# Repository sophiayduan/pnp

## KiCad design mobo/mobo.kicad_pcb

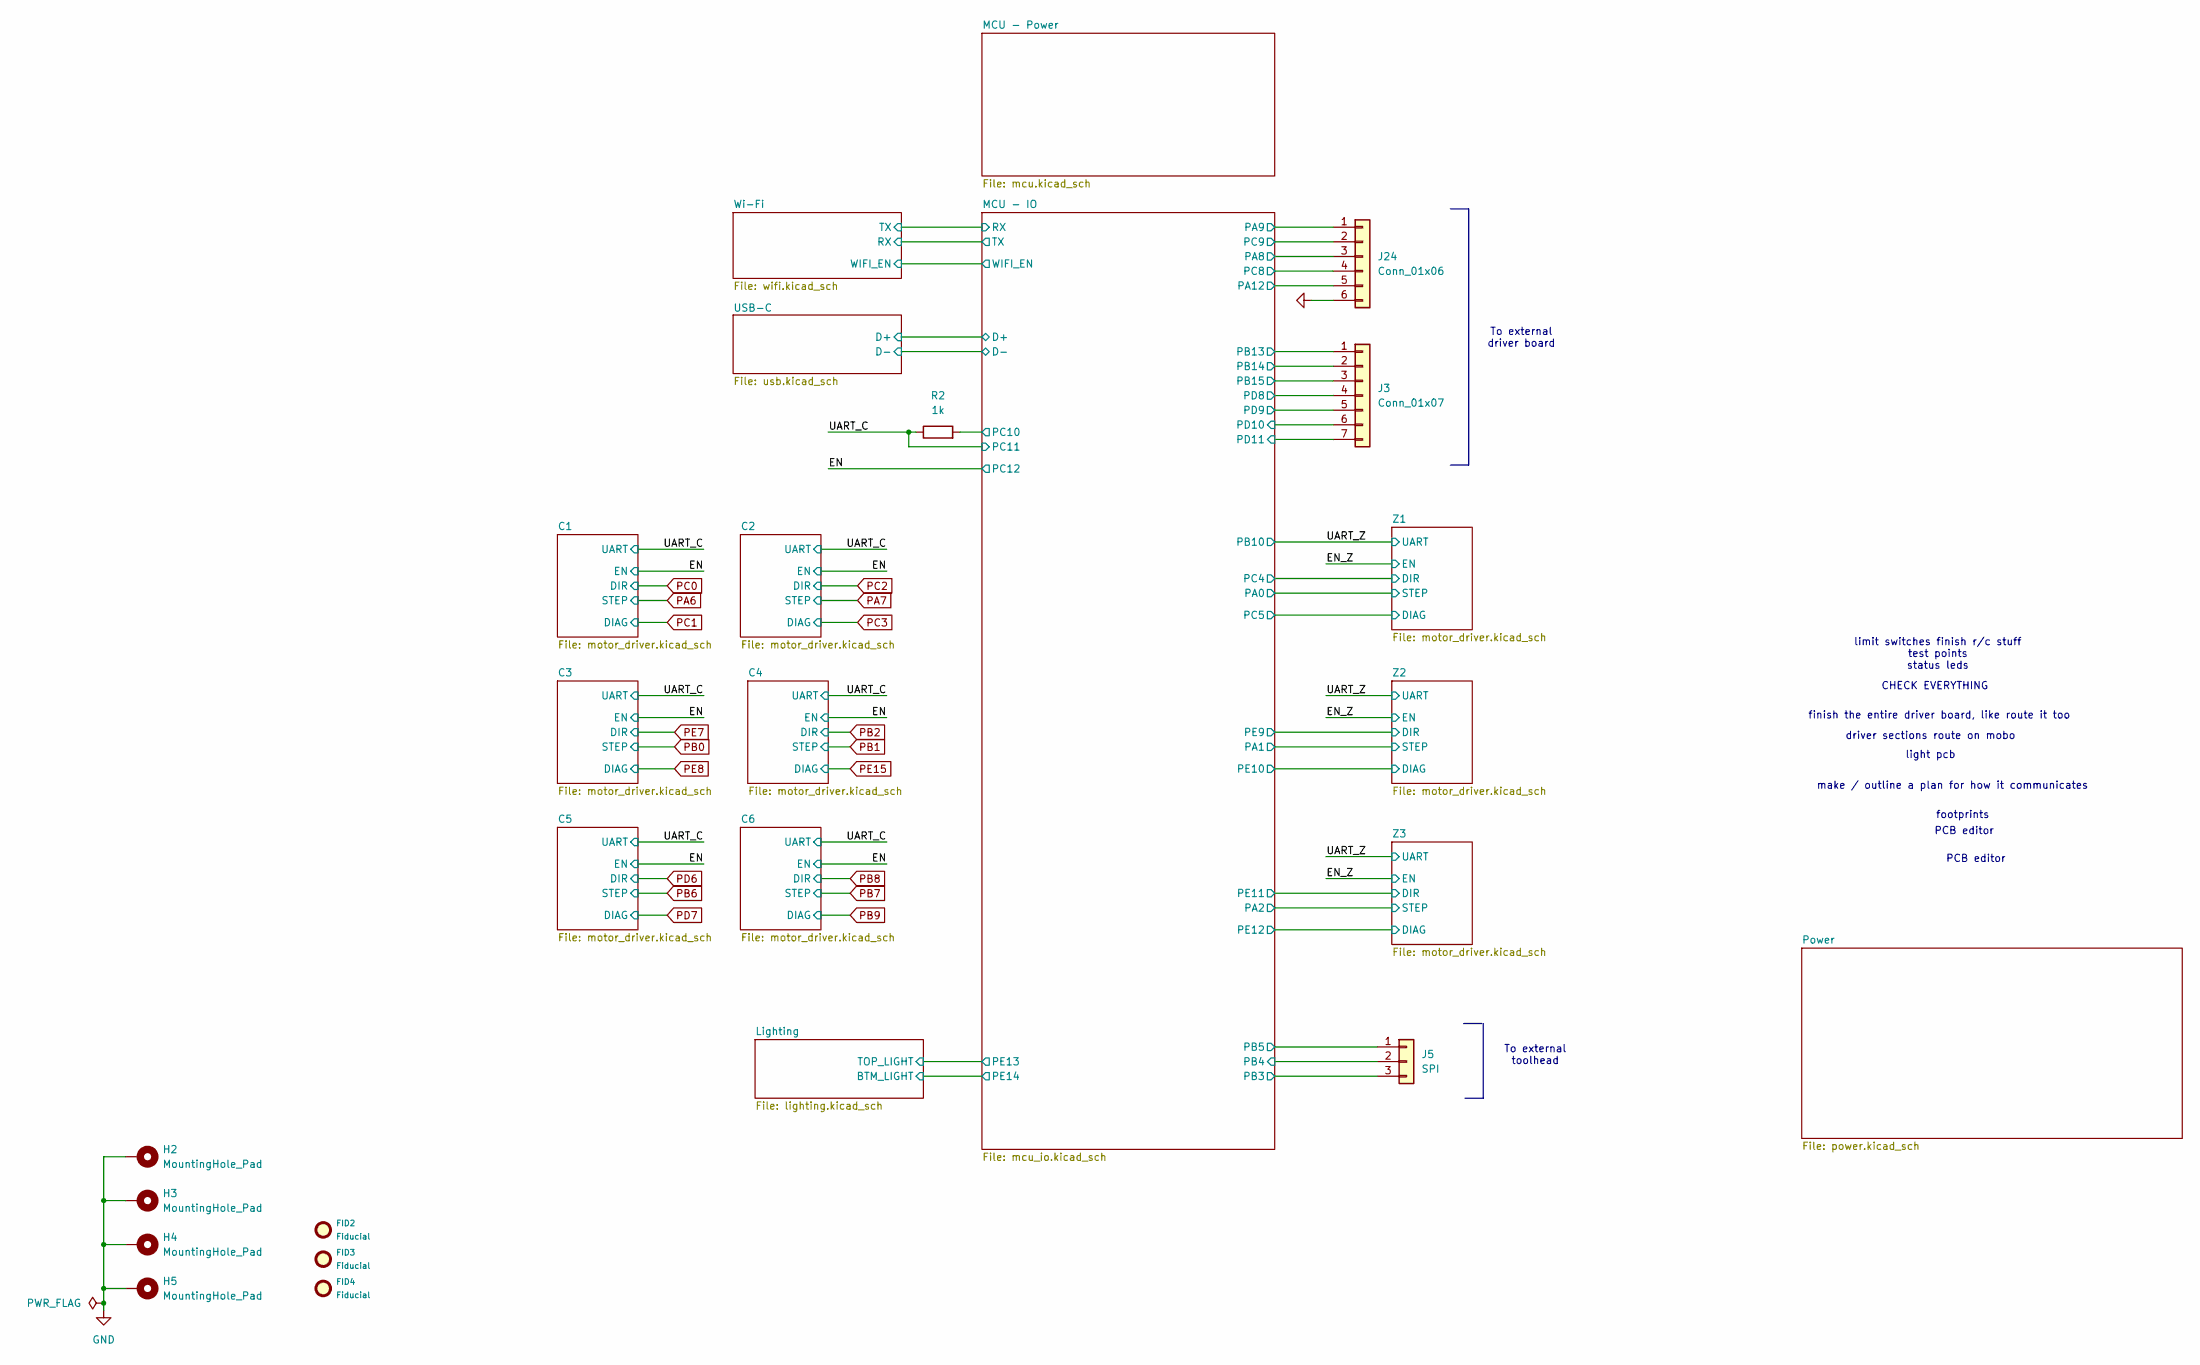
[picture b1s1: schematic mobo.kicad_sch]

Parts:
FID2, FID3, FID4: Fiducial; Fiducial_1mm_Mask2mm
H2, H3, H4, H5: MountingHole_Pad; MountingHole_2.2mm_M2_Pad_Via
J3: Conn_01x07; JST_XH_B7B-XH-A_1x07_P2.50mm_Vertical
J5: SPI; JST_EH_S3B-EH_1x03_P2.50mm_Horizontal
J24: Conn_01x06; JST_XH_B6B-XH-A_1x06_P2.50mm_Vertical
R2: 1k; R_0402_1005Metric

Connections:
/MCU - IO/PA8: J24.3; also elsewhere on the board
/MCU - IO/PA9: J24.1; also elsewhere on the board
/MCU - IO/PA12: J24.5; also elsewhere on the board
/MCU - IO/PB3: J5.3; also elsewhere on the board
/MCU - IO/PB4: J5.2; also elsewhere on the board
/MCU - IO/PB5: J5.1; also elsewhere on the board
/MCU - IO/PB13: J3.1; also elsewhere on the board
/MCU - IO/PB14: J3.2; also elsewhere on the board
/MCU - IO/PB15: J3.3; also elsewhere on the board
/MCU - IO/PC8: J24.4; also elsewhere on the board
/MCU - IO/PC9: J24.2; also elsewhere on the board
/MCU - IO/PC10: R2.2; also elsewhere on the board
/MCU - IO/PD8: J3.4; also elsewhere on the board
/MCU - IO/PD9: J3.5; also elsewhere on the board
/MCU - IO/PD10: J3.6; also elsewhere on the board
/MCU - IO/PD11: J3.7; also elsewhere on the board
/UART_C: R2.1; also elsewhere on the board
GND: H2.1, H3.1, H4.1, H5.1, J24.6; also elsewhere on the board

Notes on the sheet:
driver sections route on mobo
PCB editor
To external toolhead
light pcb
limit switches finish r/c stuff test points status leds
CHECK EVERYTHING
To external driver board
footprints
finish the entire driver board, like route it too
make / outline a plan for how it communicates

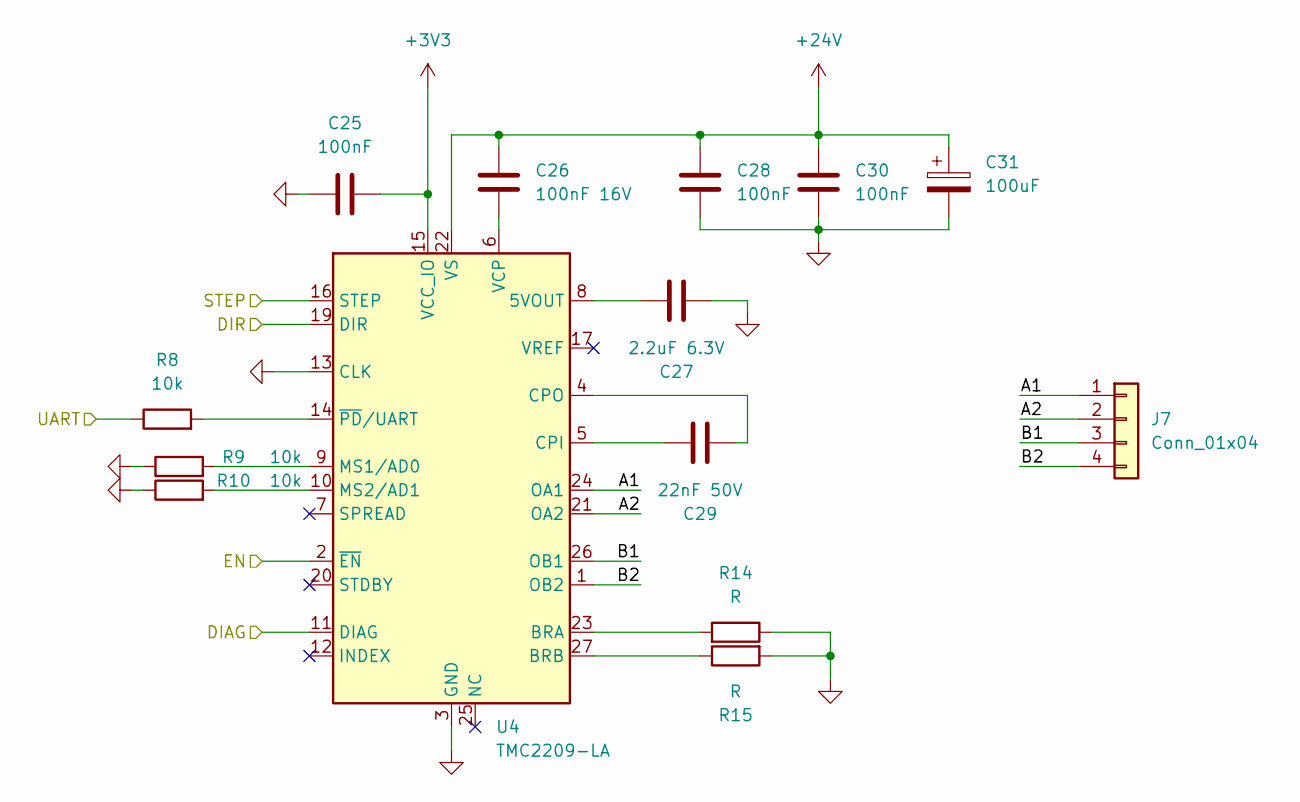
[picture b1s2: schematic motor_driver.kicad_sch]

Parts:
C25, C28: 100nF; C_0603_1608Metric
C26: 100nF 16V; C_0402_1005Metric
C27: 2.2uF 6.3V; C_0805_2012Metric
C29: 22nF 50V; C_0402_1005Metric
C30: 100nF; C_0402_1005Metric
C31: 100uF; CP_Elec_6.3x5.8
J7: Conn_01x04; JST_PH_B4B-PH-SM4-TB_1x04-1MP_P2.00mm_Vertical
R8, R9, R10: 10k; R_0402_1005Metric
R14, R15: R; R_1206_3216Metric
U4: TMC2209-LA; VQFN-28-1EP_5x5mm_P0.5mm_EP3.7x3.7mm_ThermalVias

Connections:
+3V3: C25.2, U4.15 (VCC_IO); also elsewhere on the board
+24V: C26.2, C28.2, C30.2, C31.1, U4.22 (VS), U4.28 (VS); also elsewhere on the board
/EN_Z: U4.2 (~EN); also elsewhere on the board
/MCU - IO/PA1: U4.16 (STEP); also elsewhere on the board
/MCU - IO/PE9: U4.19 (DIR); also elsewhere on the board
/MCU - IO/PE10: U4.11 (DIAG); also elsewhere on the board
/UART_Z: R8.1; also elsewhere on the board
/Z2/A1: J7.1, U4.24 (OA1)
/Z2/A2: J7.2, U4.21 (OA2)
/Z2/B1: J7.3, U4.26 (OB1)
/Z2/B2: J7.4, U4.1 (OB2)
GND: C25.1, C27.2, C28.1, C30.1, C31.2, R9.1, R10.1, R14.1, R15.2, U4.3 (GND), U4.13 (CLK), U4.18 (GND), U4.29 (GND); also elsewhere on the board
unnamed: C27.1, U4.8 (5VOUT)
unnamed: R14.2, U4.23 (BRA)
unnamed: R15.1, U4.27 (BRB)
unnamed: C29.2, U4.5 (CPI)
unnamed: C29.1, U4.4 (CPO)
unnamed: R9.2, U4.9 (MS1/AD0)
unnamed: R10.2, U4.10 (MS2/AD1)
unnamed: C26.1, U4.6 (VCP)
unnamed: R8.2, U4.14 (~PD/UART)

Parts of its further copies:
C32, C35, C46, C50, C53, C56, C60, C63, C69, C72, C76, C79, C83, C86, C121, C124: 100nF; C_0603_1608Metric
C33, C47, C54, C61, C70, C77, C84, C122: 100nF 16V; C_0402_1005Metric
C34, C48, C55, C62, C71, C78, C85, C123: 2.2uF 6.3V; C_0805_2012Metric
C36, C49, C57, C64, C73, C80, C87, C125: 22nF 50V; C_0402_1005Metric
C37, C51, C58, C65, C74, C81, C88, C126: 100nF; C_0402_1005Metric
C38, C52, C59, C66, C75, C82, C89, C127: 100uF; CP_Elec_6.3x5.8
J8, J10, J11, J12, J14, J15, J16, J22: Conn_01x04; JST_PH_B4B-PH-SM4-TB_1x04-1MP_P2.00mm_Vertical
R11, R12, R13, R17, R18, R19, R22, R23, R24, R25, R26, R29, R32, R33, R34, R37, R38, R39, R40, R41, R44, R72, R73, R74: 10k; R_0402_1005Metric
R16, R20, R21, R27, R28, R30, R31, R35, R36, R42, R43, R45, R46, R66, R75, R76: R; R_1206_3216Metric
U5, U7, U8, U9, U10, U11, U12, U19: TMC2209-LA; VQFN-28-1EP_5x5mm_P0.5mm_EP3.7x3.7mm_ThermalVias

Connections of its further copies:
+3V3: C32.2, C46.2, C53.2, C60.2, C69.2, C76.2, C83.2, C121.2, U5.15 (VCC_IO), U7.15 (VCC_IO), U8.15 (VCC_IO), U9.15 (VCC_IO), U10.15 (VCC_IO), U11.15 (VCC_IO), U12.15 (VCC_IO), U19.15 (VCC_IO); also elsewhere on the board
+24V: C33.2, C35.2, C37.2, C38.1, C47.2, C50.2, C51.2, C52.1, C54.2, C56.2, C58.2, C59.1, C61.2, C63.2, C65.2, C66.1, C70.2, C72.2, C74.2, C75.1, C77.2, C79.2, C81.2, C82.1, C84.2, C86.2, C88.2, C89.1, C122.2, C124.2, C126.2, C127.1, U5.22 (VS), U5.28 (VS), U7.22 (VS), U7.28 (VS), U8.22 (VS), U8.28 (VS), U9.22 (VS), U9.28 (VS), U10.22 (VS), U10.28 (VS), U11.22 (VS), U11.28 (VS), U12.22 (VS), U12.28 (VS), U19.22 (VS), U19.28 (VS); also elsewhere on the board
/C1/A1: J11.1, U8.24 (OA1)
/C1/A2: J11.2, U8.21 (OA2)
/C1/B1: J11.3, U8.26 (OB1)
/C1/B2: J11.4, U8.1 (OB2)
/C2/A1: J10.1, U7.24 (OA1)
/C2/A2: J10.2, U7.21 (OA2)
/C2/B1: J10.3, U7.26 (OB1)
/C2/B2: J10.4, U7.1 (OB2)
/C3/A1: J12.1, U9.24 (OA1)
/C3/A2: J12.2, U9.21 (OA2)
/C3/B1: J12.3, U9.26 (OB1)
/C3/B2: J12.4, U9.1 (OB2)
/C4/A1: J14.1, U10.24 (OA1)
/C4/A2: J14.2, U10.21 (OA2)
/C4/B1: J14.3, U10.26 (OB1)
/C4/B2: J14.4, U10.1 (OB2)
/C5/A1: J16.1, U12.24 (OA1)
/C5/A2: J16.2, U12.21 (OA2)
/C5/B1: J16.3, U12.26 (OB1)
/C5/B2: J16.4, U12.1 (OB2)
/C6/A1: J15.1, U11.24 (OA1)
/C6/A2: J15.2, U11.21 (OA2)
/C6/B1: J15.3, U11.26 (OB1)
/C6/B2: J15.4, U11.1 (OB2)
/EN: U7.2 (~EN), U8.2 (~EN), U9.2 (~EN), U10.2 (~EN), U11.2 (~EN), U12.2 (~EN); also elsewhere on the board
/EN_Z: U5.2 (~EN), U19.2 (~EN); also elsewhere on the board
/MCU - IO/PA0: U19.16 (STEP); also elsewhere on the board
/MCU - IO/PA2: U5.16 (STEP); also elsewhere on the board
/MCU - IO/PC4: U19.19 (DIR); also elsewhere on the board
/MCU - IO/PC5: U19.11 (DIAG); also elsewhere on the board
/MCU - IO/PE11: U5.19 (DIR); also elsewhere on the board
/MCU - IO/PE12: U5.11 (DIAG); also elsewhere on the board
/UART_C: R17.1, R22.1, R23.1, R32.1, R37.1, R38.1; also elsewhere on the board
/UART_Z: R11.1, R72.1; also elsewhere on the board
/Z1/A1: J22.1, U19.24 (OA1)
/Z1/A2: J22.2, U19.21 (OA2)
/Z1/B1: J22.3, U19.26 (OB1)
/Z1/B2: J22.4, U19.1 (OB2)
/Z3/A1: J8.1, U5.24 (OA1)
/Z3/A2: J8.2, U5.21 (OA2)
/Z3/B1: J8.3, U5.26 (OB1)
/Z3/B2: J8.4, U5.1 (OB2)
GND: C32.1, C34.2, C35.1, C37.1, C38.2, C46.1, C48.2, C50.1, C51.1, C52.2, C53.1, C55.2, C56.1, C58.1, C59.2, C60.1, C62.2, C63.1, C65.1, C66.2, C69.1, C71.2, C72.1, C74.1, C75.2, C76.1, C78.2, C79.1, C81.1, C82.2, C83.1, C85.2, C86.1, C88.1, C89.2, C121.1, C123.2, C124.1, C126.1, C127.2, R12.1, R13.1, R16.1, R18.1, R19.1, R20.1, R21.2, R24.1, R25.1, R26.1, R27.1, R28.2, R29.1, R30.1, R31.2, R33.1, R34.1, R35.1, R36.2, R39.1, R40.1, R41.1, R42.1, R43.2, R44.1, R45.1, R46.2, R66.2, R73.1, R74.1, R75.1, R76.2, U5.3 (GND), U5.13 (CLK), U5.18 (GND), U5.29 (GND), U7.3 (GND), U7.13 (CLK), U7.18 (GND), U7.29 (GND), U8.3 (GND), U8.13 (CLK), U8.18 (GND), U8.29 (GND), U9.3 (GND), U9.13 (CLK), U9.18 (GND), U9.29 (GND), U10.3 (GND), U10.13 (CLK), U10.18 (GND), U10.29 (GND), U11.3 (GND), U11.13 (CLK), U11.18 (GND), U11.29 (GND), U12.3 (GND), U12.13 (CLK), U12.18 (GND), U12.29 (GND), U19.3 (GND), U19.13 (CLK), U19.18 (GND), U19.29 (GND); also elsewhere on the board
unnamed: C34.1, U5.8 (5VOUT)
unnamed: R16.2, U5.23 (BRA)
unnamed: R66.1, U5.27 (BRB)
unnamed: C36.2, U5.5 (CPI)
unnamed: C36.1, U5.4 (CPO)
unnamed: R12.2, U5.9 (MS1/AD0)
unnamed: R13.2, U5.10 (MS2/AD1)
unnamed: C33.1, U5.6 (VCP)
unnamed: R11.2, U5.14 (~PD/UART)
unnamed: C48.1, U7.8 (5VOUT)
unnamed: R20.2, U7.23 (BRA)
unnamed: R21.1, U7.27 (BRB)
unnamed: C49.2, U7.5 (CPI)
unnamed: C49.1, U7.4 (CPO)
unnamed: R18.2, U7.9 (MS1/AD0)
unnamed: R19.2, U7.10 (MS2/AD1)
unnamed: C47.1, U7.6 (VCP)
unnamed: R17.2, U7.14 (~PD/UART)
unnamed: C55.1, U8.8 (5VOUT)
unnamed: R27.2, U8.23 (BRA)
unnamed: R28.1, U8.27 (BRB)
unnamed: C57.2, U8.5 (CPI)
unnamed: C57.1, U8.4 (CPO)
unnamed: R25.2, U8.9 (MS1/AD0)
unnamed: R26.2, U8.10 (MS2/AD1)
unnamed: C54.1, U8.6 (VCP)
unnamed: R22.2, U8.14 (~PD/UART)
unnamed: C62.1, U9.8 (5VOUT)
unnamed: R30.2, U9.23 (BRA)
unnamed: R31.1, U9.27 (BRB)
unnamed: C64.2, U9.5 (CPI)
unnamed: C64.1, U9.4 (CPO)
unnamed: R24.2, U9.9 (MS1/AD0)
unnamed: R29.2, U9.10 (MS2/AD1)
unnamed: C61.1, U9.6 (VCP)
unnamed: R23.2, U9.14 (~PD/UART)
unnamed: C71.1, U10.8 (5VOUT)
unnamed: R35.2, U10.23 (BRA)
unnamed: R36.1, U10.27 (BRB)
unnamed: C73.2, U10.5 (CPI)
unnamed: C73.1, U10.4 (CPO)
unnamed: R33.2, U10.9 (MS1/AD0)
unnamed: R34.2, U10.10 (MS2/AD1)
unnamed: C70.1, U10.6 (VCP)
unnamed: R32.2, U10.14 (~PD/UART)
unnamed: C78.1, U11.8 (5VOUT)
unnamed: R42.2, U11.23 (BRA)
unnamed: R43.1, U11.27 (BRB)
unnamed: C80.2, U11.5 (CPI)
unnamed: C80.1, U11.4 (CPO)
unnamed: R40.2, U11.9 (MS1/AD0)
unnamed: R41.2, U11.10 (MS2/AD1)
unnamed: C77.1, U11.6 (VCP)
unnamed: R37.2, U11.14 (~PD/UART)
unnamed: C85.1, U12.8 (5VOUT)
unnamed: R45.2, U12.23 (BRA)
unnamed: R46.1, U12.27 (BRB)
unnamed: C87.2, U12.5 (CPI)
unnamed: C87.1, U12.4 (CPO)
unnamed: R39.2, U12.9 (MS1/AD0)
unnamed: R44.2, U12.10 (MS2/AD1)
unnamed: C84.1, U12.6 (VCP)
unnamed: R38.2, U12.14 (~PD/UART)
unnamed: C123.1, U19.8 (5VOUT)
unnamed: R75.2, U19.23 (BRA)
unnamed: R76.1, U19.27 (BRB)
unnamed: C125.2, U19.5 (CPI)
unnamed: C125.1, U19.4 (CPO)
unnamed: R73.2, U19.9 (MS1/AD0)
unnamed: R74.2, U19.10 (MS2/AD1)
unnamed: C122.1, U19.6 (VCP)
unnamed: R72.2, U19.14 (~PD/UART)
PA6: U8.16 (STEP); also elsewhere on the board
PA7: U7.16 (STEP); also elsewhere on the board
PB0: U9.16 (STEP); also elsewhere on the board
PB1: U10.16 (STEP); also elsewhere on the board
PB2: U10.19 (DIR); also elsewhere on the board
PB6: U12.16 (STEP); also elsewhere on the board
PB7: U11.16 (STEP); also elsewhere on the board
PB8: U11.19 (DIR); also elsewhere on the board
PB9: U11.11 (DIAG); also elsewhere on the board
PC0: U8.19 (DIR); also elsewhere on the board
PC1: U8.11 (DIAG); also elsewhere on the board
PC2: U7.19 (DIR); also elsewhere on the board
PC3: U7.11 (DIAG); also elsewhere on the board
PD6: U12.19 (DIR); also elsewhere on the board
PD7: U12.11 (DIAG); also elsewhere on the board
PE7: U9.19 (DIR); also elsewhere on the board
PE8: U9.11 (DIAG); also elsewhere on the board
PE15: U10.11 (DIAG); also elsewhere on the board

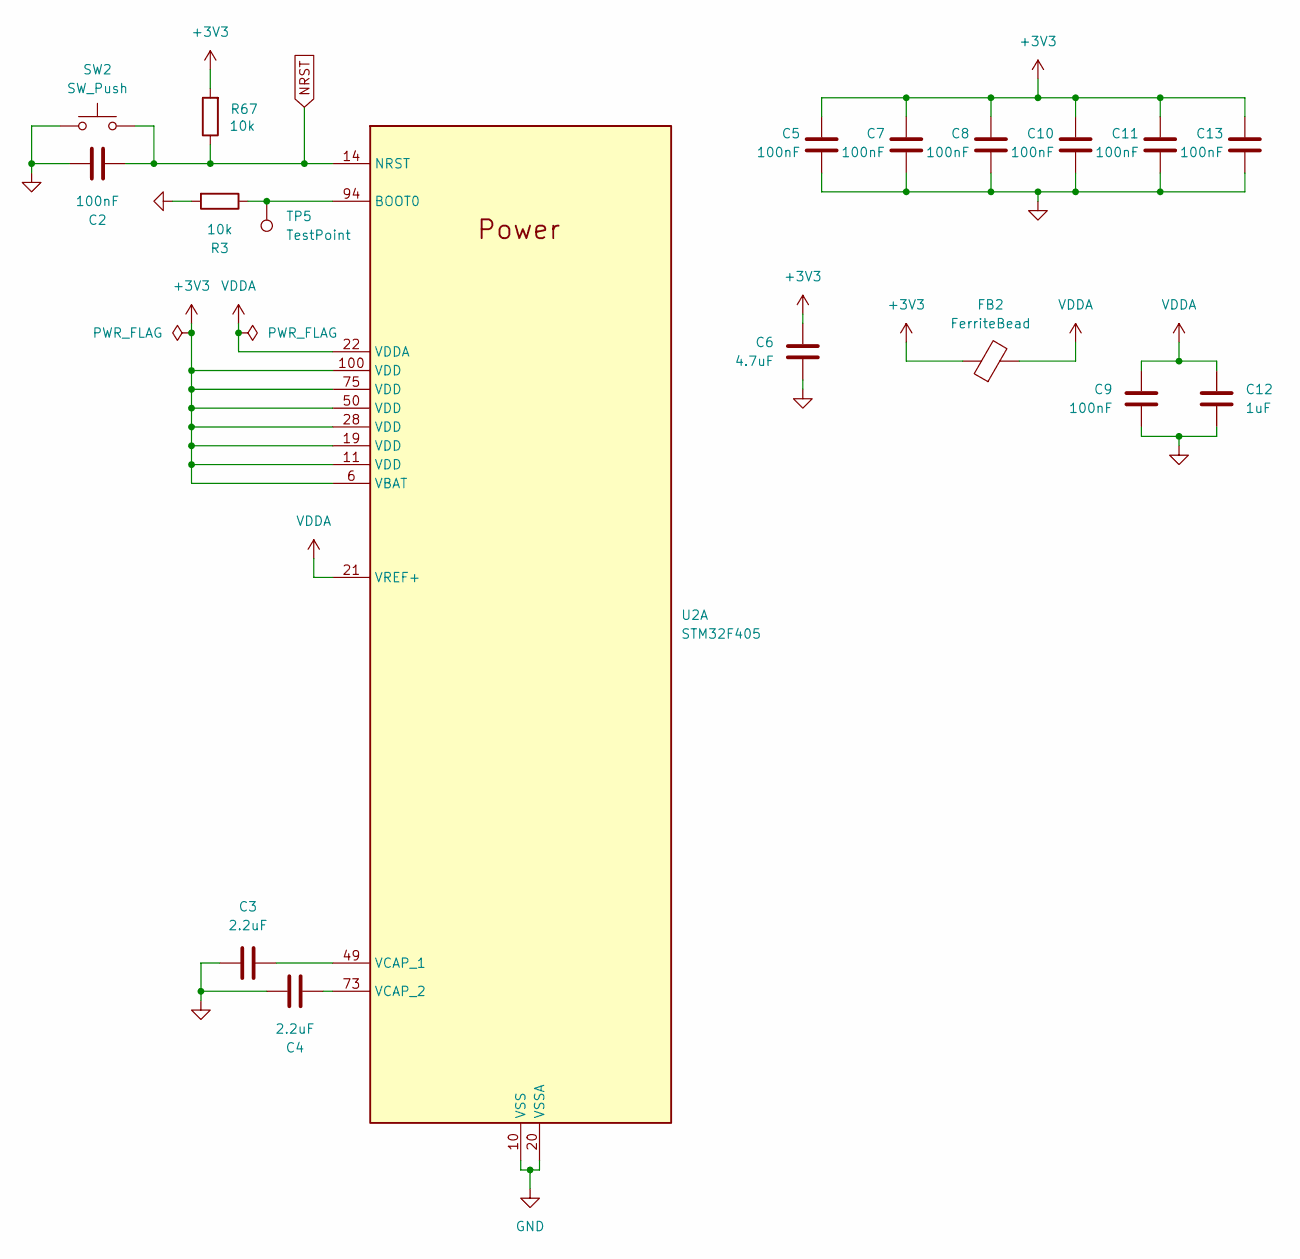
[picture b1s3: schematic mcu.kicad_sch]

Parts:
C2, C5, C7, C8, C9, C10, C11, C13: 100nF; C_0402_1005Metric
C3, C4: 2.2uF; C_0603_1608Metric
C6: 4.7uF; C_0402_1005Metric
C12: 1uF; C_0402_1005Metric
FB2: FerriteBead; L_0402_1005Metric
R3, R67: 10k; R_0402_1005Metric
SW2: SW_Push; SW_SPST_TS-1088-xR020
TP5: TestPoint; TestPoint_Pad_D2.0mm
U2: STM32F405; LQFP-100_L14.0-W14.0-P0.50-LS16.0-BL

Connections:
+3V3: C5.1, C6.1, C7.1, C8.1, C10.1, C11.1, C13.1, FB2.1, R67.2, U2.6 (VBAT), U2.11 (VDD), U2.19 (VDD), U2.28 (VDD), U2.50 (VDD), U2.75 (VDD), U2.100 (VDD); also elsewhere on the board
GND: C2.2, C3.1, C4.1, C5.2, C6.2, C7.2, C8.2, C9.2, C10.2, C11.2, C12.2, C13.2, R3.2, SW2.1, U2.10 (VSS), U2.20 (VSSA), U2.27 (VSS), U2.74 (VSS), U2.99 (VSS); also elsewhere on the board
NRST: C2.1, R67.1, SW2.2, U2.14 (NRST); also elsewhere on the board
unnamed: R3.1, TP5.1, U2.94 (BOOT0)
unnamed: C3.2, U2.49 (VCAP_1)
unnamed: C4.2, U2.73 (VCAP_2)
VDDA: C9.1, C12.1, FB2.2, U2.21 (VREF+), U2.22 (VDDA)

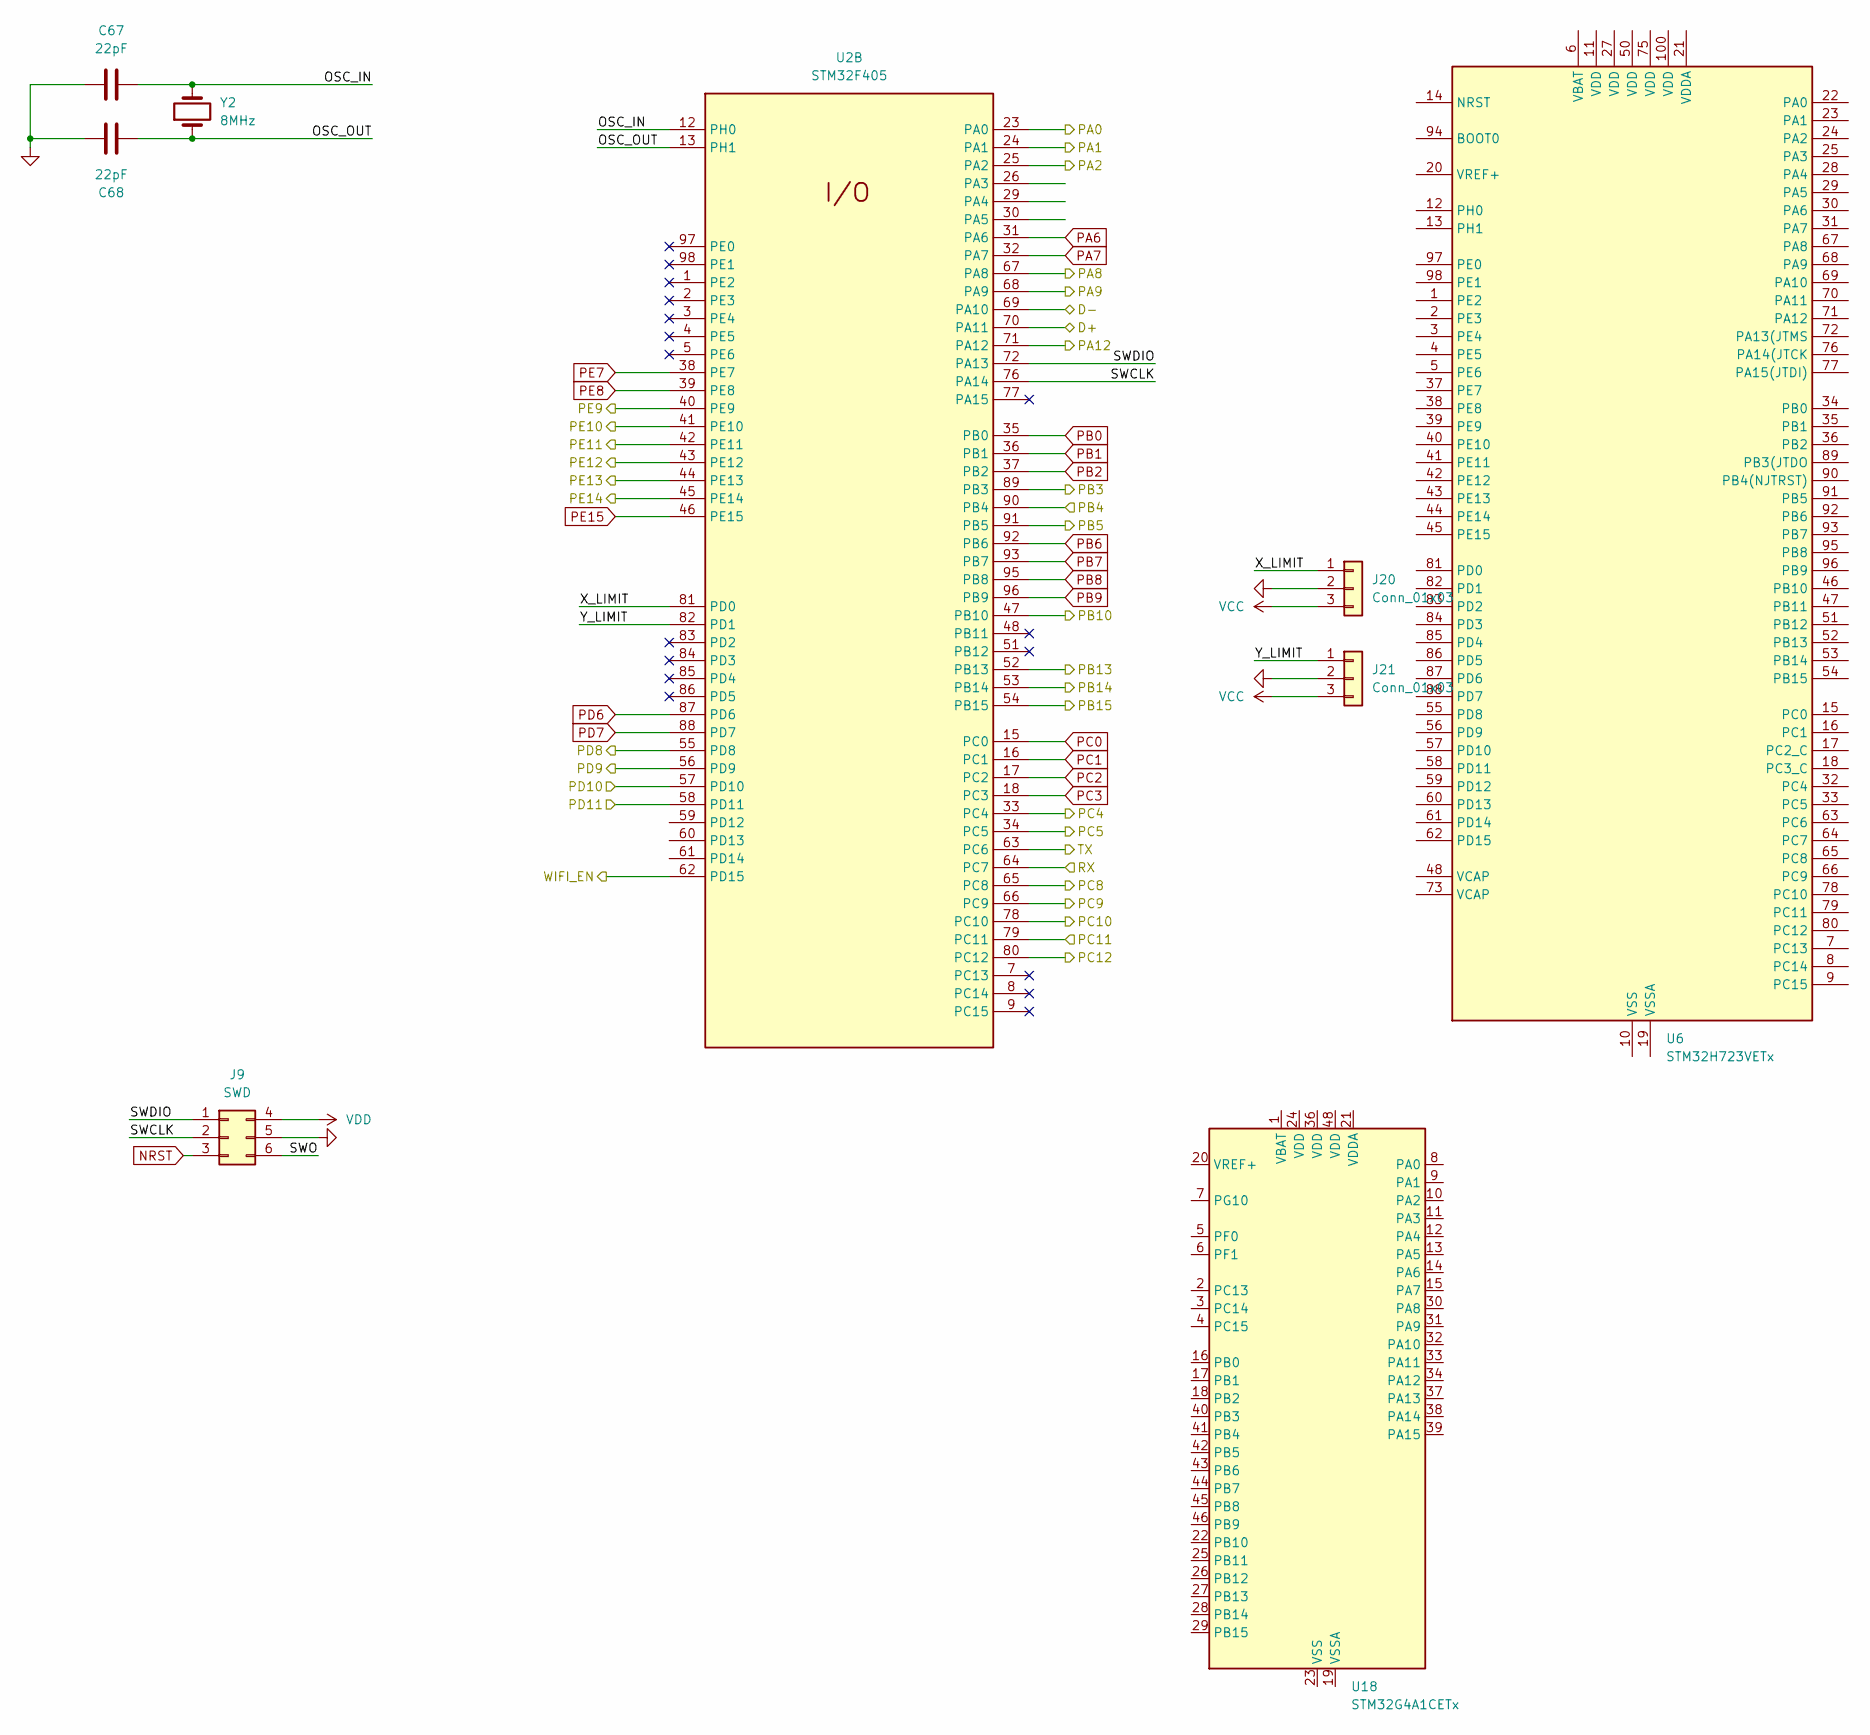
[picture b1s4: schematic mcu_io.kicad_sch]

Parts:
C67, C68: 22pF; C_0402_1005Metric
J9: SWD; PinHeader_2x03_P2.00mm_Vertical
J20, J21: Conn_01x03; JST_PH_B3B-PH-SM4-TB_1x03-1MP_P2.00mm_Vertical
U2: STM32F405; LQFP-100_L14.0-W14.0-P0.50-LS16.0-BL
U6: STM32H723VETx; LQFP-100_14x14mm_P0.5mm
U18: STM32G4A1CETx; LQFP-48_7x7mm_P0.5mm
Y2: 8MHz; Crystal_SMD_3225-4Pin_3.2x2.5mm

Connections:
/EN: U2.80 (PC12); also elsewhere on the board
/Lighting/BTM_LIGHT: U2.45 (PE14); also elsewhere on the board
/Lighting/TOP_LIGHT: U2.44 (PE13); also elsewhere on the board
/MCU - IO/D+: U2.70 (PA11); also elsewhere on the board
/MCU - IO/D-: U2.69 (PA10); also elsewhere on the board
/MCU - IO/OSC_IN: C67.2, U2.12 (PH0), Y2.2
/MCU - IO/OSC_OUT: C68.1, U2.13 (PH1), Y2.1
/MCU - IO/PA0: U2.23 (PA0); also elsewhere on the board
/MCU - IO/PA1: U2.24 (PA1); also elsewhere on the board
/MCU - IO/PA2: U2.25 (PA2); also elsewhere on the board
/MCU - IO/PA8: U2.67 (PA8); also elsewhere on the board
/MCU - IO/PA9: U2.68 (PA9); also elsewhere on the board
/MCU - IO/PA12: U2.71 (PA12); also elsewhere on the board
/MCU - IO/PB3: U2.89 (PB3); also elsewhere on the board
/MCU - IO/PB4: U2.90 (PB4); also elsewhere on the board
/MCU - IO/PB5: U2.91 (PB5); also elsewhere on the board
/MCU - IO/PB13: U2.52 (PB13); also elsewhere on the board
/MCU - IO/PB14: U2.53 (PB14); also elsewhere on the board
/MCU - IO/PB15: U2.54 (PB15); also elsewhere on the board
/MCU - IO/PC4: U2.33 (PC4); also elsewhere on the board
/MCU - IO/PC5: U2.34 (PC5); also elsewhere on the board
/MCU - IO/PC8: U2.65 (PC8); also elsewhere on the board
/MCU - IO/PC9: U2.66 (PC9); also elsewhere on the board
/MCU - IO/PC10: U2.78 (PC10); also elsewhere on the board
/MCU - IO/PD8: U2.55 (PD8); also elsewhere on the board
/MCU - IO/PD9: U2.56 (PD9); also elsewhere on the board
/MCU - IO/PD10: U2.57 (PD10); also elsewhere on the board
/MCU - IO/PD11: U2.58 (PD11); also elsewhere on the board
/MCU - IO/PE9: U2.40 (PE9); also elsewhere on the board
/MCU - IO/PE10: U2.41 (PE10); also elsewhere on the board
/MCU - IO/PE11: U2.42 (PE11); also elsewhere on the board
/MCU - IO/PE12: U2.43 (PE12); also elsewhere on the board
/MCU - IO/RX: U2.64 (PC7); also elsewhere on the board
/MCU - IO/SWCLK: J9.2, U2.76 (PA14)
/MCU - IO/SWDIO: J9.1, U2.72 (PA13)
/MCU - IO/SWO: J9.6
/MCU - IO/TX: U2.63 (PC6); also elsewhere on the board
/MCU - IO/WIFI_EN: U2.62 (PD15); also elsewhere on the board
/MCU - IO/X_LIMIT: J20.1, U2.81 (PD0)
/MCU - IO/Y_LIMIT: J21.1, U2.82 (PD1)
/UART_C: U2.79 (PC11); also elsewhere on the board
/UART_Z: U2.47 (PB10); also elsewhere on the board
GND: C67.1, C68.2, J9.5, J20.2, J21.2; also elsewhere on the board
NRST: J9.3; also elsewhere on the board
unnamed: U6.10 (VSS), U6.26 (VSS), U6.49 (VSS), U6.74 (VSS), U6.99 (VSS)
unnamed: U18.23 (VSS), U18.35 (VSS), U18.47 (VSS)
PA6: U2.31 (PA6); also elsewhere on the board
PA7: U2.32 (PA7); also elsewhere on the board
PB0: U2.35 (PB0); also elsewhere on the board
PB1: U2.36 (PB1); also elsewhere on the board
PB2: U2.37 (PB2); also elsewhere on the board
PB6: U2.92 (PB6); also elsewhere on the board
PB7: U2.93 (PB7); also elsewhere on the board
PB8: U2.95 (PB8); also elsewhere on the board
PB9: U2.96 (PB9); also elsewhere on the board
PC0: U2.15 (PC0); also elsewhere on the board
PC1: U2.16 (PC1); also elsewhere on the board
PC2: U2.17 (PC2); also elsewhere on the board
PC3: U2.18 (PC3); also elsewhere on the board
PD6: U2.87 (PD6); also elsewhere on the board
PD7: U2.88 (PD7); also elsewhere on the board
PE7: U2.38 (PE7); also elsewhere on the board
PE8: U2.39 (PE8); also elsewhere on the board
PE15: U2.46 (PE15); also elsewhere on the board
VCC: J20.3, J21.3
VDD: J9.4

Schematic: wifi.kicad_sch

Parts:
C23: 22uF; C_0805_2012Metric
C24: 0.1uF; C_0402_1005Metric
R4, R5: 10k; R_0402_1005Metric
U3: ESP32-WROOM-32E; ESP32-WROOM-32D

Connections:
+3V3: C23.1, C24.1, R5.2, U3.2 (VDD); also elsewhere on the board
/MCU - IO/RX: U3.34 (RXD0/IO3); also elsewhere on the board
/MCU - IO/TX: U3.35 (TXD0/IO1); also elsewhere on the board
/MCU - IO/WIFI_EN: R4.2; also elsewhere on the board
GND: C23.2, C24.2, U3.1 (GND), U3.15 (GND), U3.38 (GND), U3.39 (GND); also elsewhere on the board
unnamed: R4.1, U3.3 (EN)
unnamed: R5.1, U3.25 (IO0)
